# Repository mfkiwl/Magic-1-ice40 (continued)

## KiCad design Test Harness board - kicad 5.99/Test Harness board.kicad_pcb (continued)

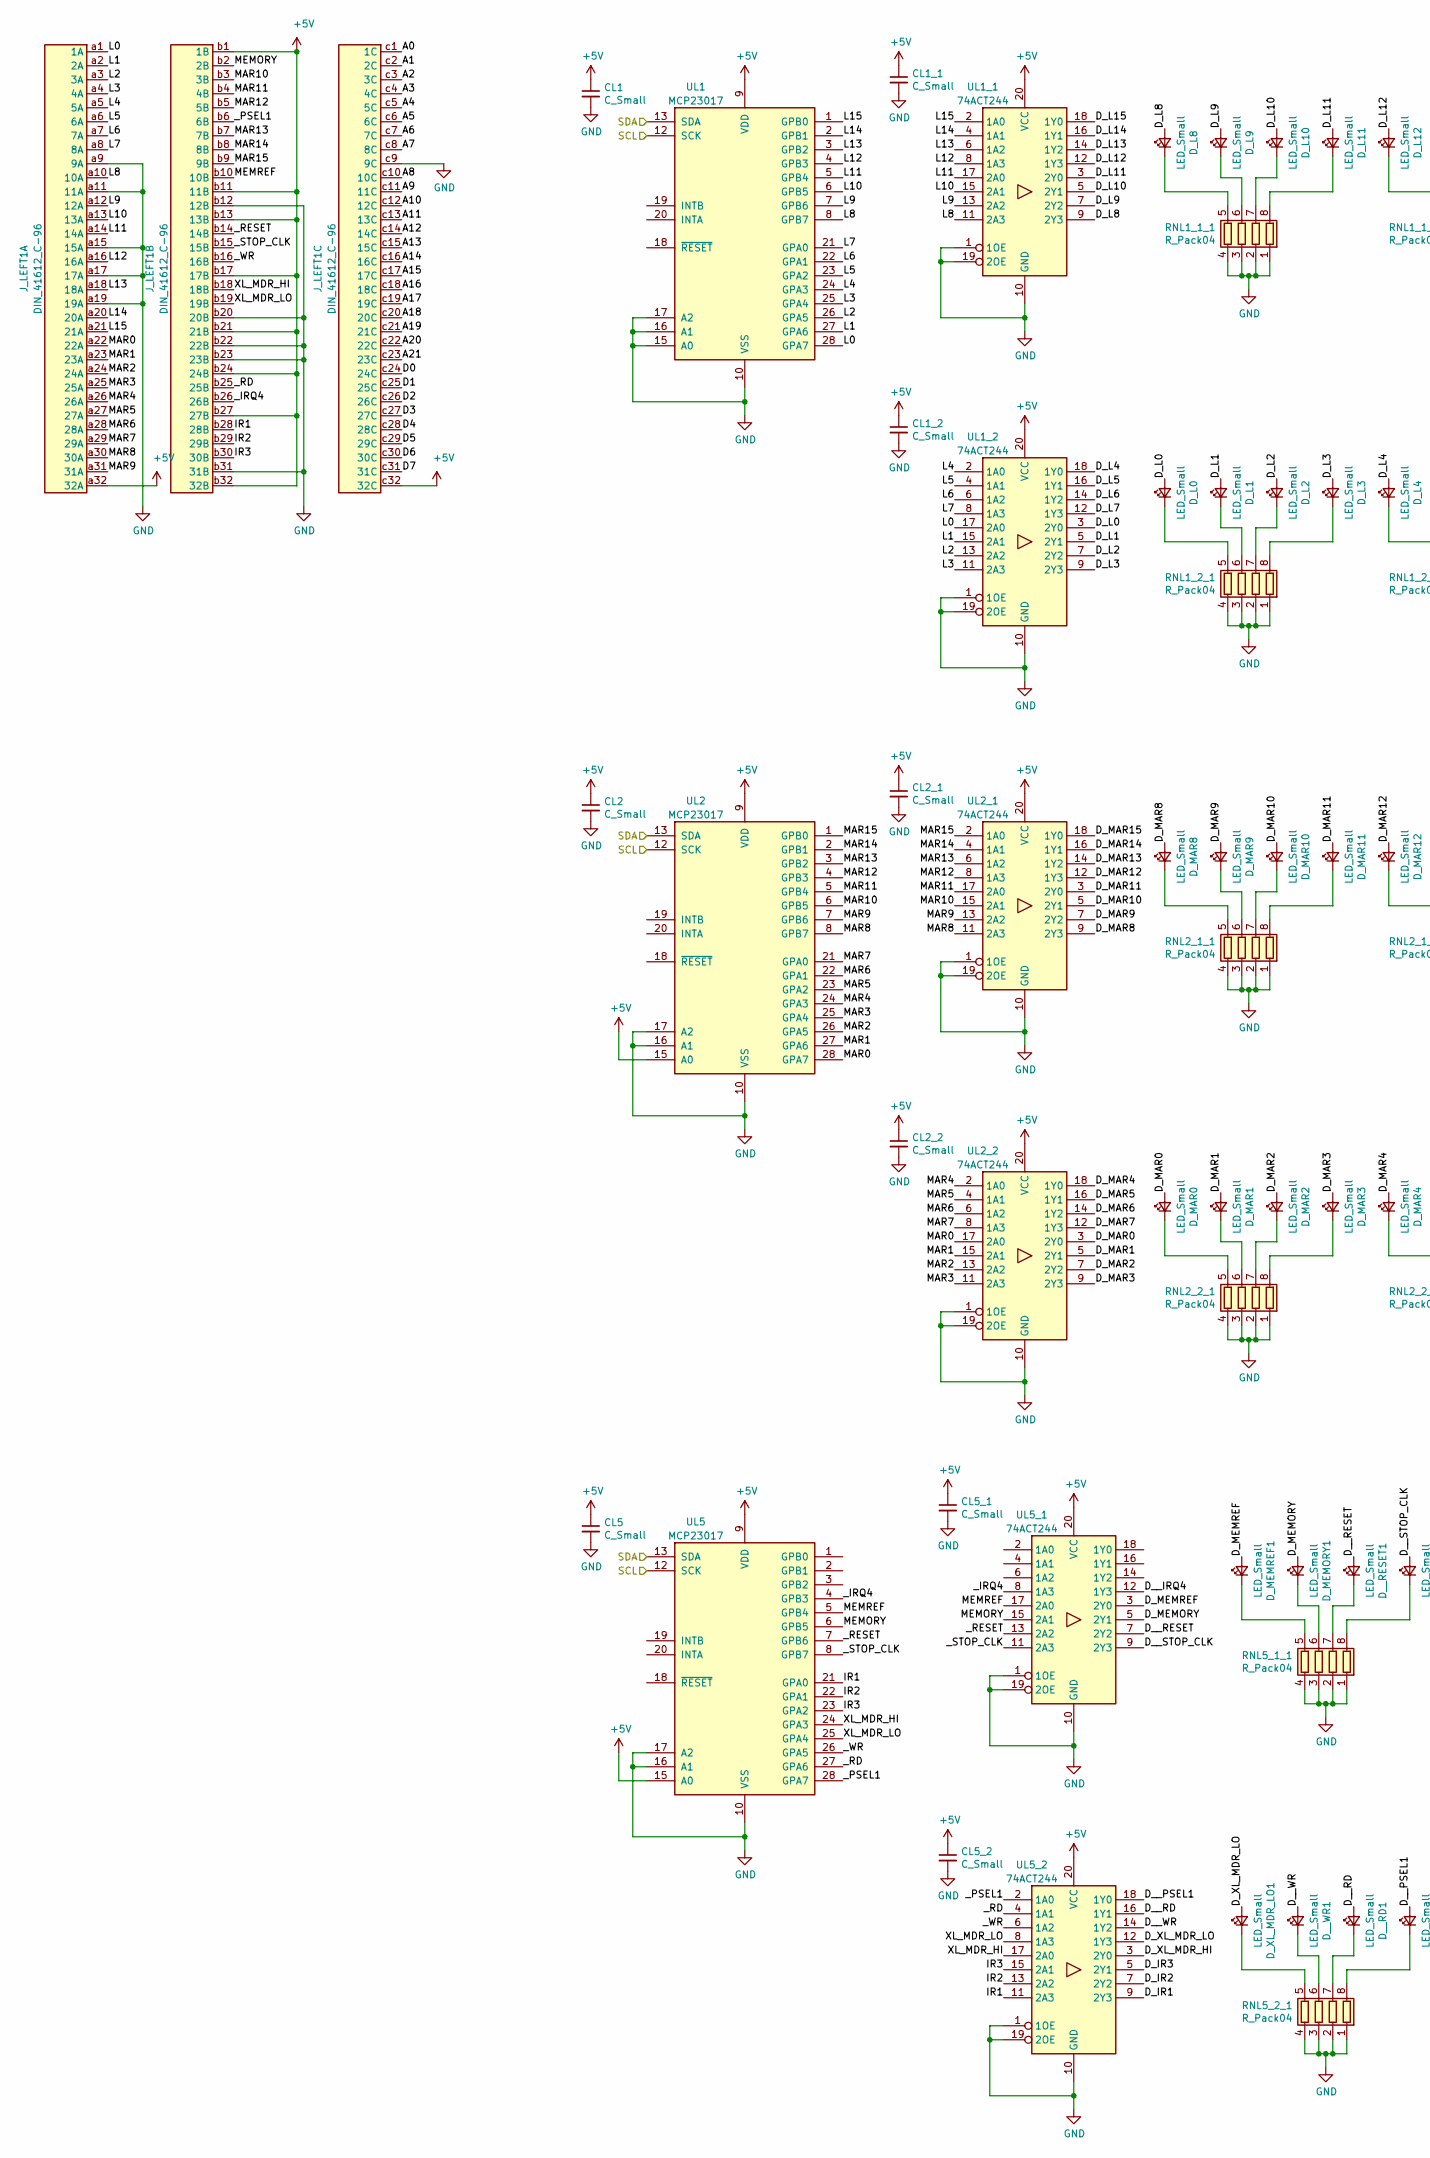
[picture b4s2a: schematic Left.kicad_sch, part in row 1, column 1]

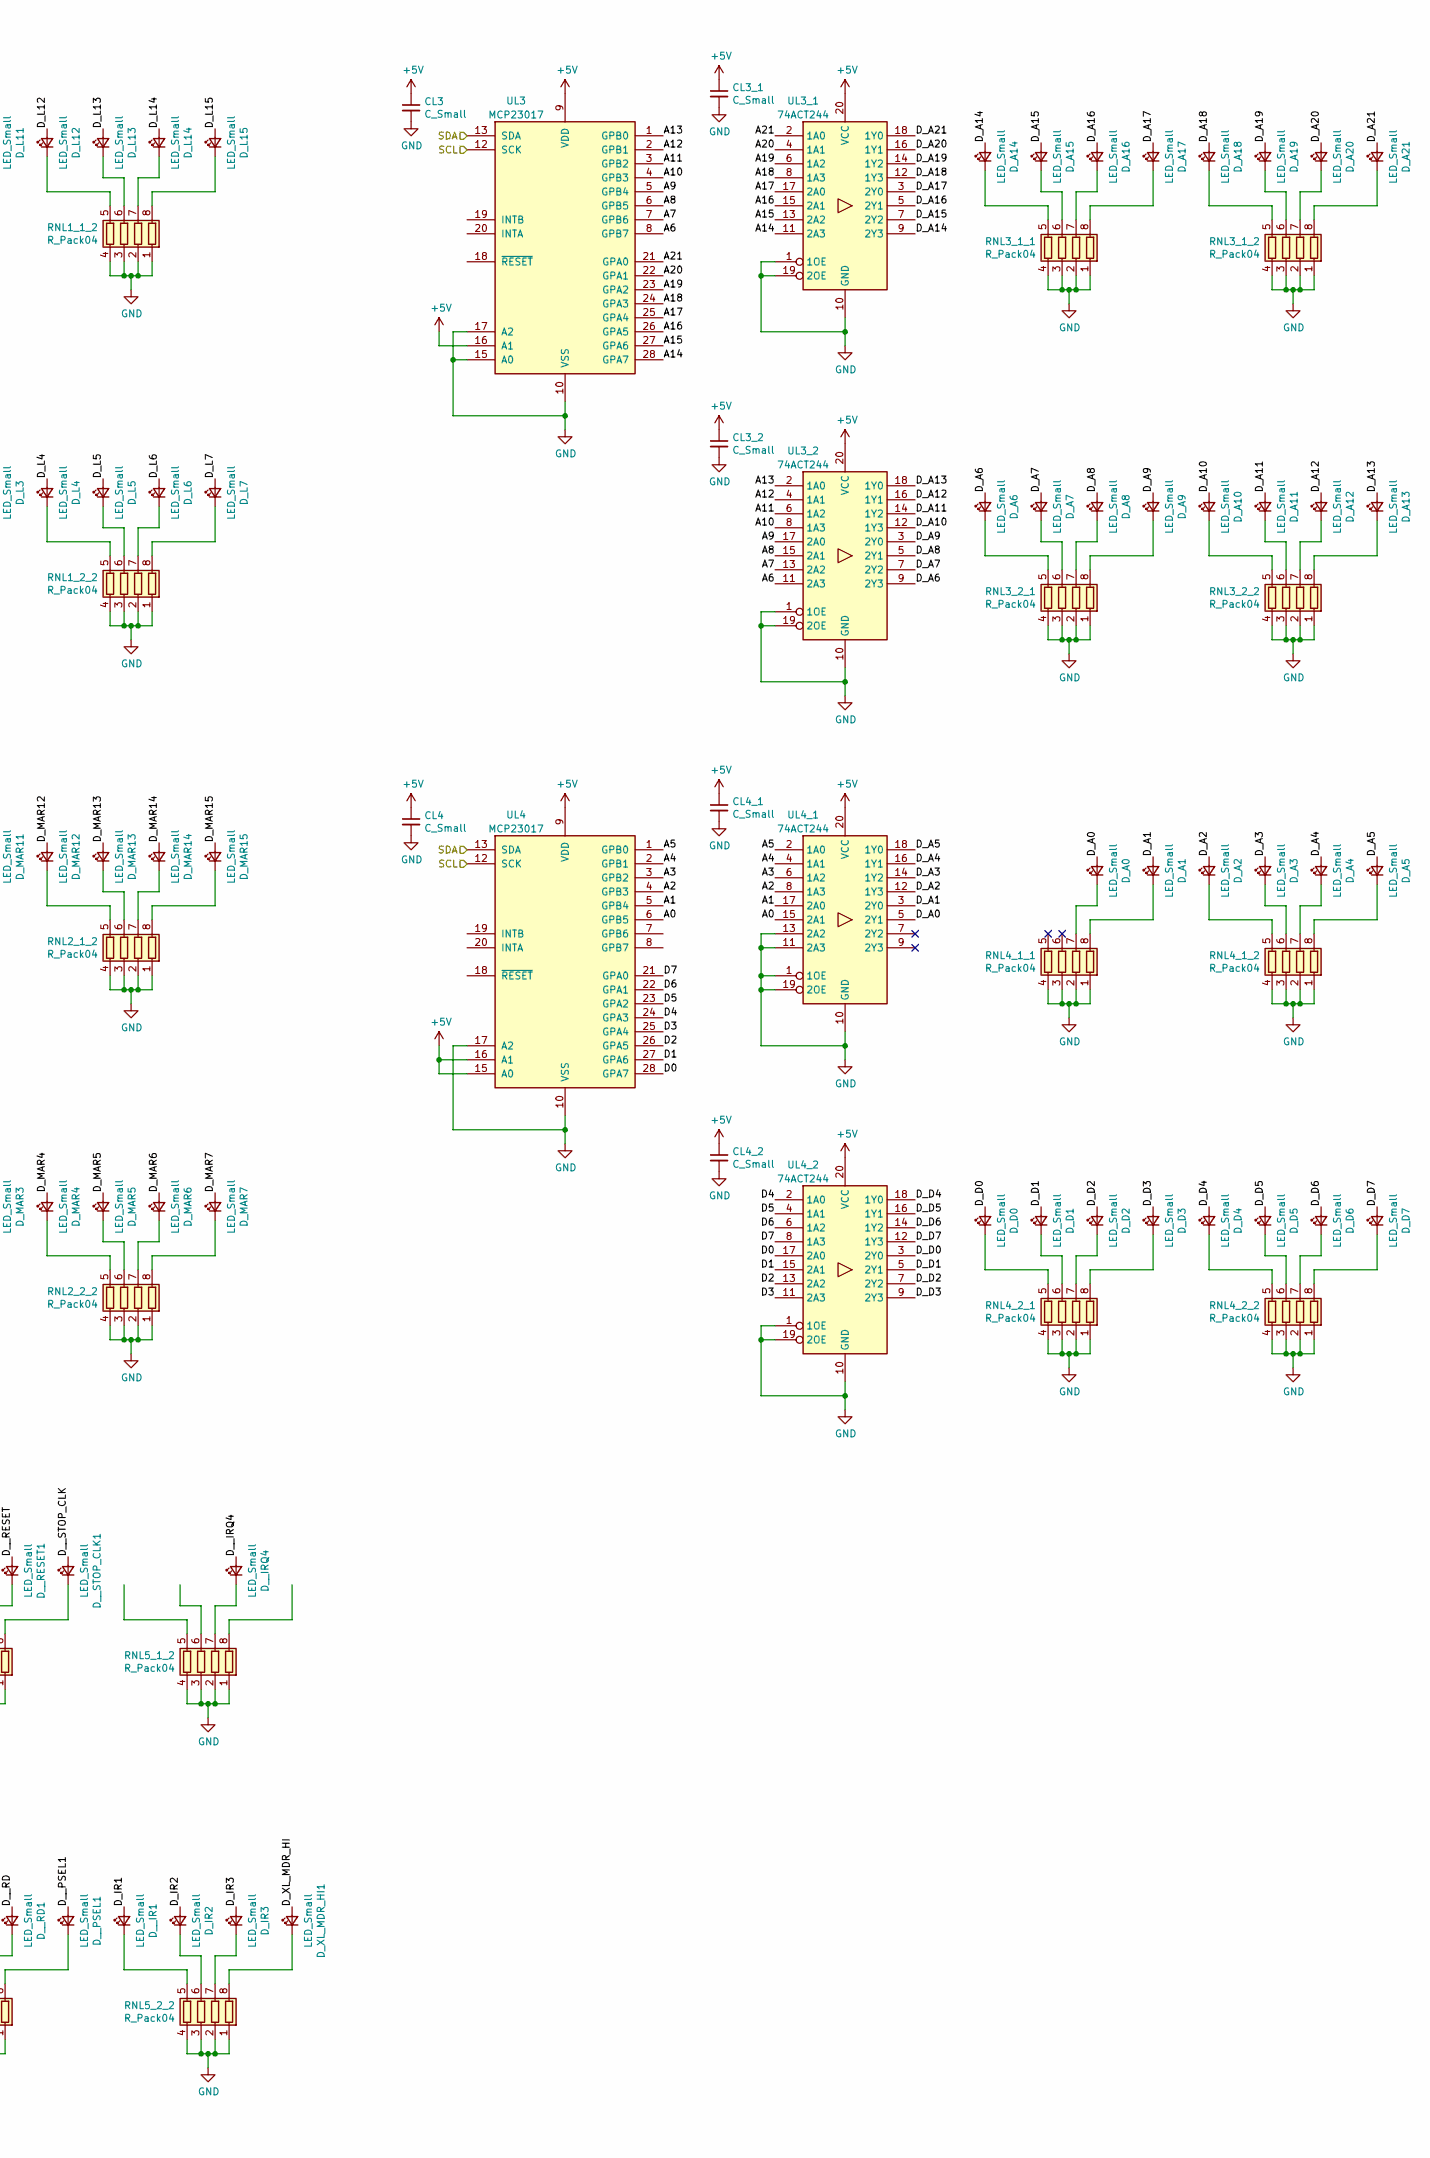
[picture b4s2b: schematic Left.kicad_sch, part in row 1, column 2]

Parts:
CL1, CL1_1, CL1_2, CL2, CL2_1, CL2_2, CL3, CL3_1, CL3_2, CL4, CL4_1, CL4_2, CL5, CL5_1, CL5_2: C_Small; C_1206_3216Metric
D_A0, D_A1, D_A2, D_A3, D_A4, D_A5, D_A6, D_A7, D_A8, D_A9, D_A10, D_A11, D_A12, D_A13, D_A14, D_A15, D_A16, D_A17, D_A18, D_A19, D_A20, D_A21: LED_Small; LED_1206_3216Metric_Castellated; Digikey 160-1167-1-ND
D_D0, D_D1, D_D2, D_D3, D_D4, D_D5, D_D6, D_D7: LED_Small; LED_1206_3216Metric_Castellated; Digikey 160-1167-1-ND
D_IR2, D_IR3: LED_Small; LED_1206_3216Metric_Castellated; Digikey 160-1167-1-ND
D_L0, D_L1, D_L2, D_L3, D_L4, D_L5, D_L6, D_L7, D_L8, D_L9, D_L10, D_L11, D_L12, D_L13, D_L14, D_L15: LED_Small; LED_1206_3216Metric_Castellated; Digikey 160-1167-1-ND
D_MAR0, D_MAR1, D_MAR2, D_MAR3, D_MAR4, D_MAR5, D_MAR6, D_MAR7, D_MAR8, D_MAR9, D_MAR10, D_MAR11, D_MAR12, D_MAR13, D_MAR14, D_MAR15: LED_Small; LED_1206_3216Metric_Castellated; Digikey 160-1167-1-ND
D_MEMORY1: LED_Small; LED_1206_3216Metric_Castellated; Digikey 160-1167-1-ND
D_MEMREF1: LED_Small; LED_1206_3216Metric_Castellated; Digikey 160-1167-1-ND
D_XL_MDR_HI1: LED_Small; LED_1206_3216Metric_Castellated; Digikey 160-1167-1-ND
D_XL_MDR_LO1: LED_Small; LED_1206_3216Metric_Castellated; Digikey 160-1167-1-ND
D__IR1: LED_Small; LED_1206_3216Metric_Castellated; Digikey 160-1167-1-ND
D__IRQ4: LED_Small; LED_1206_3216Metric_Castellated; Digikey 160-1167-1-ND
D__PSEL1: LED_Small; LED_1206_3216Metric_Castellated; Digikey 160-1167-1-ND
D__RD1: LED_Small; LED_1206_3216Metric_Castellated; Digikey 160-1167-1-ND
D__RESET1: LED_Small; LED_1206_3216Metric_Castellated; Digikey 160-1167-1-ND
D__STOP_CLK1: LED_Small; LED_1206_3216Metric_Castellated; Digikey 160-1167-1-ND
D__WR1: LED_Small; LED_1206_3216Metric_Castellated; Digikey 160-1167-1-ND
J_LEFT1: DIN_41612_C-96; DIN41612_C_3x32_Male_Horizontal_THT
RNL1_1_1, RNL1_1_2, RNL1_2_1, RNL1_2_2, RNL2_1_1, RNL2_1_2, RNL2_2_1, RNL2_2_2, RNL3_1_1, RNL3_1_2, RNL3_2_1, RNL3_2_2, RNL4_1_1, RNL4_1_2, RNL4_2_1, RNL4_2_2, RNL5_1_1, RNL5_1_2, RNL5_2_1, RNL5_2_2: R_Pack04; R_Array_Convex_4x1206; Digikey CAY16-331J4LFCT-ND
UL1, UL2, UL3, UL4, UL5: MCP23017; SOIC-28W_7.5x17.9mm_P1.27mm
UL1_1, UL1_2, UL2_1, UL2_2, UL3_1, UL3_2, UL4_1, UL4_2, UL5_1, UL5_2: 74ACT244; SOIC-20W_7.5x12.8mm_P1.27mm; Digikey 296-1071-1-ND

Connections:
+5V: CL1.1, CL1_1.1, CL1_2.1, CL2.1, CL2_1.1, CL2_2.1, CL3.1, CL3_1.1, CL3_2.1, CL4.1, CL4_1.1, CL4_2.1, CL5.1, CL5_1.1, CL5_2.1, J_LEFT1.a32 (32A), J_LEFT1.b1 (1B), J_LEFT1.b11 (11B), J_LEFT1.b13 (13B), J_LEFT1.b17 (17B), J_LEFT1.b21 (21B), J_LEFT1.b24 (24B), J_LEFT1.b27 (27B), J_LEFT1.b32 (32B), J_LEFT1.c32 (32C), UL1.9 (VDD), UL1_1.20 (VCC), UL1_2.20 (VCC), UL2.9 (VDD), UL2.15 (A0), UL2_1.20 (VCC), UL2_2.20 (VCC), UL3.9 (VDD), UL3.16 (A1), UL3_1.20 (VCC), UL3_2.20 (VCC), UL4.9 (VDD), UL4.15 (A0), UL4.16 (A1), UL4_1.20 (VCC), UL4_2.20 (VCC), UL5.9 (VDD), UL5.15 (A0), UL5_1.20 (VCC), UL5_2.20 (VCC); also elsewhere on the board
/Left connector/A0: J_LEFT1.c1 (1C), UL4.6 (GPB5), UL4_1.15 (2A1)
/Left connector/A1: J_LEFT1.c2 (2C), UL4.5 (GPB4), UL4_1.17 (2A0)
/Left connector/A2: J_LEFT1.c3 (3C), UL4.4 (GPB3), UL4_1.8 (1A3)
/Left connector/A3: J_LEFT1.c4 (4C), UL4.3 (GPB2), UL4_1.6 (1A2)
/Left connector/A4: J_LEFT1.c5 (5C), UL4.2 (GPB1), UL4_1.4 (1A1)
/Left connector/A5: J_LEFT1.c6 (6C), UL4.1 (GPB0), UL4_1.2 (1A0)
/Left connector/A6: J_LEFT1.c7 (7C), UL3.8 (GPB7), UL3_2.11 (2A3)
/Left connector/A7: J_LEFT1.c8 (8C), UL3.7 (GPB6), UL3_2.13 (2A2)
/Left connector/A8: J_LEFT1.c10 (10C), UL3.6 (GPB5), UL3_2.15 (2A1)
/Left connector/A9: J_LEFT1.c11 (11C), UL3.5 (GPB4), UL3_2.17 (2A0)
/Left connector/A10: J_LEFT1.c12 (12C), UL3.4 (GPB3), UL3_2.8 (1A3)
/Left connector/A11: J_LEFT1.c13 (13C), UL3.3 (GPB2), UL3_2.6 (1A2)
/Left connector/A12: J_LEFT1.c14 (14C), UL3.2 (GPB1), UL3_2.4 (1A1)
/Left connector/A13: J_LEFT1.c15 (15C), UL3.1 (GPB0), UL3_2.2 (1A0)
/Left connector/A14: J_LEFT1.c16 (16C), UL3.28 (GPA7), UL3_1.11 (2A3)
/Left connector/A15: J_LEFT1.c17 (17C), UL3.27 (GPA6), UL3_1.13 (2A2)
/Left connector/A16: J_LEFT1.c18 (18C), UL3.26 (GPA5), UL3_1.15 (2A1)
/Left connector/A17: J_LEFT1.c19 (19C), UL3.25 (GPA4), UL3_1.17 (2A0)
/Left connector/A18: J_LEFT1.c20 (20C), UL3.24 (GPA3), UL3_1.8 (1A3)
/Left connector/A19: J_LEFT1.c21 (21C), UL3.23 (GPA2), UL3_1.6 (1A2)
/Left connector/A20: J_LEFT1.c22 (22C), UL3.22 (GPA1), UL3_1.4 (1A1)
/Left connector/A21: J_LEFT1.c23 (23C), UL3.21 (GPA0), UL3_1.2 (1A0)
/Left connector/D0: J_LEFT1.c24 (24C), UL4.28 (GPA7), UL4_2.17 (2A0)
/Left connector/D1: J_LEFT1.c25 (25C), UL4.27 (GPA6), UL4_2.15 (2A1)
/Left connector/D2: J_LEFT1.c26 (26C), UL4.26 (GPA5), UL4_2.13 (2A2)
/Left connector/D3: J_LEFT1.c27 (27C), UL4.25 (GPA4), UL4_2.11 (2A3)
/Left connector/D4: J_LEFT1.c28 (28C), UL4.24 (GPA3), UL4_2.2 (1A0)
/Left connector/D5: J_LEFT1.c29 (29C), UL4.23 (GPA2), UL4_2.4 (1A1)
/Left connector/D6: J_LEFT1.c30 (30C), UL4.22 (GPA1), UL4_2.6 (1A2)
/Left connector/D7: J_LEFT1.c31 (31C), UL4.21 (GPA0), UL4_2.8 (1A3)
/Left connector/D_A0: D_A0.2 (A), UL4_1.5 (2Y1)
/Left connector/D_A1: D_A1.2 (A), UL4_1.3 (2Y0)
/Left connector/D_A2: D_A2.2 (A), UL4_1.12 (1Y3)
/Left connector/D_A3: D_A3.2 (A), UL4_1.14 (1Y2)
/Left connector/D_A4: D_A4.2 (A), UL4_1.16 (1Y1)
/Left connector/D_A5: D_A5.2 (A), UL4_1.18 (1Y0)
/Left connector/D_A6: D_A6.2 (A), UL3_2.9 (2Y3)
/Left connector/D_A7: D_A7.2 (A), UL3_2.7 (2Y2)
/Left connector/D_A8: D_A8.2 (A), UL3_2.5 (2Y1)
/Left connector/D_A9: D_A9.2 (A), UL3_2.3 (2Y0)
/Left connector/D_A10: D_A10.2 (A), UL3_2.12 (1Y3)
/Left connector/D_A11: D_A11.2 (A), UL3_2.14 (1Y2)
/Left connector/D_A12: D_A12.2 (A), UL3_2.16 (1Y1)
/Left connector/D_A13: D_A13.2 (A), UL3_2.18 (1Y0)
/Left connector/D_A14: D_A14.2 (A), UL3_1.9 (2Y3)
/Left connector/D_A15: D_A15.2 (A), UL3_1.7 (2Y2)
/Left connector/D_A16: D_A16.2 (A), UL3_1.5 (2Y1)
/Left connector/D_A17: D_A17.2 (A), UL3_1.3 (2Y0)
/Left connector/D_A18: D_A18.2 (A), UL3_1.12 (1Y3)
/Left connector/D_A19: D_A19.2 (A), UL3_1.14 (1Y2)
/Left connector/D_A20: D_A20.2 (A), UL3_1.16 (1Y1)
/Left connector/D_A21: D_A21.2 (A), UL3_1.18 (1Y0)
/Left connector/D_D0: D_D0.2 (A), UL4_2.3 (2Y0)
/Left connector/D_D1: D_D1.2 (A), UL4_2.5 (2Y1)
/Left connector/D_D2: D_D2.2 (A), UL4_2.7 (2Y2)
/Left connector/D_D3: D_D3.2 (A), UL4_2.9 (2Y3)
/Left connector/D_D4: D_D4.2 (A), UL4_2.18 (1Y0)
/Left connector/D_D5: D_D5.2 (A), UL4_2.16 (1Y1)
/Left connector/D_D6: D_D6.2 (A), UL4_2.14 (1Y2)
/Left connector/D_D7: D_D7.2 (A), UL4_2.12 (1Y3)
/Left connector/D_IR1: D__IR1.2 (A), UL5_2.9 (2Y3)
/Left connector/D_IR2: D_IR2.2 (A), UL5_2.7 (2Y2)
/Left connector/D_IR3: D_IR3.2 (A), UL5_2.5 (2Y1)
/Left connector/D_L0: D_L0.2 (A), UL1_2.3 (2Y0)
/Left connector/D_L1: D_L1.2 (A), UL1_2.5 (2Y1)
/Left connector/D_L2: D_L2.2 (A), UL1_2.7 (2Y2)
/Left connector/D_L3: D_L3.2 (A), UL1_2.9 (2Y3)
/Left connector/D_L4: D_L4.2 (A), UL1_2.18 (1Y0)
/Left connector/D_L5: D_L5.2 (A), UL1_2.16 (1Y1)
/Left connector/D_L6: D_L6.2 (A), UL1_2.14 (1Y2)
/Left connector/D_L7: D_L7.2 (A), UL1_2.12 (1Y3)
/Left connector/D_L8: D_L8.2 (A), UL1_1.9 (2Y3)
/Left connector/D_L9: D_L9.2 (A), UL1_1.7 (2Y2)
/Left connector/D_L10: D_L10.2 (A), UL1_1.5 (2Y1)
/Left connector/D_L11: D_L11.2 (A), UL1_1.3 (2Y0)
/Left connector/D_L12: D_L12.2 (A), UL1_1.12 (1Y3)
/Left connector/D_L13: D_L13.2 (A), UL1_1.14 (1Y2)
/Left connector/D_L14: D_L14.2 (A), UL1_1.16 (1Y1)
/Left connector/D_L15: D_L15.2 (A), UL1_1.18 (1Y0)
/Left connector/D_MAR0: D_MAR0.2 (A), UL2_2.3 (2Y0)
/Left connector/D_MAR1: D_MAR1.2 (A), UL2_2.5 (2Y1)
/Left connector/D_MAR2: D_MAR2.2 (A), UL2_2.7 (2Y2)
/Left connector/D_MAR3: D_MAR3.2 (A), UL2_2.9 (2Y3)
/Left connector/D_MAR4: D_MAR4.2 (A), UL2_2.18 (1Y0)
/Left connector/D_MAR5: D_MAR5.2 (A), UL2_2.16 (1Y1)
/Left connector/D_MAR6: D_MAR6.2 (A), UL2_2.14 (1Y2)
/Left connector/D_MAR7: D_MAR7.2 (A), UL2_2.12 (1Y3)
/Left connector/D_MAR8: D_MAR8.2 (A), UL2_1.9 (2Y3)
/Left connector/D_MAR9: D_MAR9.2 (A), UL2_1.7 (2Y2)
/Left connector/D_MAR10: D_MAR10.2 (A), UL2_1.5 (2Y1)
/Left connector/D_MAR11: D_MAR11.2 (A), UL2_1.3 (2Y0)
/Left connector/D_MAR12: D_MAR12.2 (A), UL2_1.12 (1Y3)
/Left connector/D_MAR13: D_MAR13.2 (A), UL2_1.14 (1Y2)
/Left connector/D_MAR14: D_MAR14.2 (A), UL2_1.16 (1Y1)
/Left connector/D_MAR15: D_MAR15.2 (A), UL2_1.18 (1Y0)
/Left connector/D_MEMORY: D_MEMORY1.2 (A), UL5_1.5 (2Y1)
/Left connector/D_MEMREF: D_MEMREF1.2 (A), UL5_1.3 (2Y0)
/Left connector/D_XL_MDR_HI: D_XL_MDR_HI1.2 (A), UL5_2.3 (2Y0)
/Left connector/D_XL_MDR_LO: D_XL_MDR_LO1.2 (A), UL5_2.12 (1Y3)
/Left connector/D__IRQ4: D__IRQ4.2 (A), UL5_1.12 (1Y3)
/Left connector/D__PSEL1: D__PSEL1.2 (A), UL5_2.18 (1Y0)
/Left connector/D__RD: D__RD1.2 (A), UL5_2.16 (1Y1)
/Left connector/D__RESET: D__RESET1.2 (A), UL5_1.7 (2Y2)
/Left connector/D__STOP_CLK: D__STOP_CLK1.2 (A), UL5_1.9 (2Y3)
/Left connector/D__WR: D__WR1.2 (A), UL5_2.14 (1Y2)
/Left connector/IR1: J_LEFT1.b28 (28B), UL5.21 (GPA0), UL5_2.11 (2A3)
/Left connector/IR2: J_LEFT1.b29 (29B), UL5.22 (GPA1), UL5_2.13 (2A2)
/Left connector/IR3: J_LEFT1.b30 (30B), UL5.23 (GPA2), UL5_2.15 (2A1)
/Left connector/L0: J_LEFT1.a1 (1A), UL1.28 (GPA7), UL1_2.17 (2A0)
/Left connector/L1: J_LEFT1.a2 (2A), UL1.27 (GPA6), UL1_2.15 (2A1)
/Left connector/L2: J_LEFT1.a3 (3A), UL1.26 (GPA5), UL1_2.13 (2A2)
/Left connector/L3: J_LEFT1.a4 (4A), UL1.25 (GPA4), UL1_2.11 (2A3)
/Left connector/L4: J_LEFT1.a5 (5A), UL1.24 (GPA3), UL1_2.2 (1A0)
/Left connector/L5: J_LEFT1.a6 (6A), UL1.23 (GPA2), UL1_2.4 (1A1)
/Left connector/L6: J_LEFT1.a7 (7A), UL1.22 (GPA1), UL1_2.6 (1A2)
/Left connector/L7: J_LEFT1.a8 (8A), UL1.21 (GPA0), UL1_2.8 (1A3)
/Left connector/L8: J_LEFT1.a10 (10A), UL1.8 (GPB7), UL1_1.11 (2A3)
/Left connector/L9: J_LEFT1.a12 (12A), UL1.7 (GPB6), UL1_1.13 (2A2)
/Left connector/L10: J_LEFT1.a13 (13A), UL1.6 (GPB5), UL1_1.15 (2A1)
/Left connector/L11: J_LEFT1.a14 (14A), UL1.5 (GPB4), UL1_1.17 (2A0)
/Left connector/L12: J_LEFT1.a16 (16A), UL1.4 (GPB3), UL1_1.8 (1A3)
/Left connector/L13: J_LEFT1.a18 (18A), UL1.3 (GPB2), UL1_1.6 (1A2)
/Left connector/L14: J_LEFT1.a20 (20A), UL1.2 (GPB1), UL1_1.4 (1A1)
/Left connector/L15: J_LEFT1.a21 (21A), UL1.1 (GPB0), UL1_1.2 (1A0)
/Left connector/MAR0: J_LEFT1.a22 (22A), UL2.28 (GPA7), UL2_2.17 (2A0)
/Left connector/MAR1: J_LEFT1.a23 (23A), UL2.27 (GPA6), UL2_2.15 (2A1)
/Left connector/MAR2: J_LEFT1.a24 (24A), UL2.26 (GPA5), UL2_2.13 (2A2)
/Left connector/MAR3: J_LEFT1.a25 (25A), UL2.25 (GPA4), UL2_2.11 (2A3)
/Left connector/MAR4: J_LEFT1.a26 (26A), UL2.24 (GPA3), UL2_2.2 (1A0)
/Left connector/MAR5: J_LEFT1.a27 (27A), UL2.23 (GPA2), UL2_2.4 (1A1)
/Left connector/MAR6: J_LEFT1.a28 (28A), UL2.22 (GPA1), UL2_2.6 (1A2)
/Left connector/MAR7: J_LEFT1.a29 (29A), UL2.21 (GPA0), UL2_2.8 (1A3)
/Left connector/MAR8: J_LEFT1.a30 (30A), UL2.8 (GPB7), UL2_1.11 (2A3)
/Left connector/MAR9: J_LEFT1.a31 (31A), UL2.7 (GPB6), UL2_1.13 (2A2)
/Left connector/MAR10: J_LEFT1.b3 (3B), UL2.6 (GPB5), UL2_1.15 (2A1)
/Left connector/MAR11: J_LEFT1.b4 (4B), UL2.5 (GPB4), UL2_1.17 (2A0)
/Left connector/MAR12: J_LEFT1.b5 (5B), UL2.4 (GPB3), UL2_1.8 (1A3)
/Left connector/MAR13: J_LEFT1.b7 (7B), UL2.3 (GPB2), UL2_1.6 (1A2)
/Left connector/MAR14: J_LEFT1.b8 (8B), UL2.2 (GPB1), UL2_1.4 (1A1)
/Left connector/MAR15: J_LEFT1.b9 (9B), UL2.1 (GPB0), UL2_1.2 (1A0)
/Left connector/MEMORY: J_LEFT1.b2 (2B), UL5.6 (GPB5), UL5_1.15 (2A1)
/Left connector/MEMREF: J_LEFT1.b10 (10B), UL5.5 (GPB4), UL5_1.17 (2A0)
/Left connector/SCL: UL1.12 (SCK), UL2.12 (SCK), UL3.12 (SCK), UL4.12 (SCK), UL5.12 (SCK)
/Left connector/SDA: UL1.13 (SDA), UL2.13 (SDA), UL3.13 (SDA), UL4.13 (SDA), UL5.13 (SDA)
/Left connector/XL_MDR_HI: J_LEFT1.b18 (18B), UL5.24 (GPA3), UL5_2.17 (2A0)
/Left connector/XL_MDR_LO: J_LEFT1.b19 (19B), UL5.25 (GPA4), UL5_2.8 (1A3)
/Left connector/_IRQ4: J_LEFT1.b26 (26B), UL5.4 (GPB3), UL5_1.8 (1A3)
/Left connector/_PSEL1: J_LEFT1.b6 (6B), UL5.28 (GPA7), UL5_2.2 (1A0)
/Left connector/_RD: J_LEFT1.b25 (25B), UL5.27 (GPA6), UL5_2.4 (1A1)
/Left connector/_RESET: J_LEFT1.b14 (14B), UL5.7 (GPB6), UL5_1.13 (2A2)
/Left connector/_STOP_CLK: J_LEFT1.b15 (15B), UL5.8 (GPB7), UL5_1.11 (2A3)
/Left connector/_WR: J_LEFT1.b16 (16B), UL5.26 (GPA5), UL5_2.6 (1A2)
GND: CL1.2, CL1_1.2, CL1_2.2, CL2.2, CL2_1.2, CL2_2.2, CL3.2, CL3_1.2, CL3_2.2, CL4.2, CL4_1.2, CL4_2.2, CL5.2, CL5_1.2, CL5_2.2, J_LEFT1.a9 (9A), J_LEFT1.a11 (11A), J_LEFT1.a15 (15A), J_LEFT1.a17 (17A), J_LEFT1.a19 (19A), J_LEFT1.b12 (12B), J_LEFT1.b20 (20B), J_LEFT1.b22 (22B), J_LEFT1.b23 (23B), J_LEFT1.b31 (31B), J_LEFT1.c9 (9C), RNL1_1_1.1 (R1.1), RNL1_1_1.2 (R2.1), RNL1_1_1.3 (R3.1), RNL1_1_1.4 (R4.1), RNL1_1_2.1 (R1.1), RNL1_1_2.2 (R2.1), RNL1_1_2.3 (R3.1), RNL1_1_2.4 (R4.1), RNL1_2_1.1 (R1.1), RNL1_2_1.2 (R2.1), RNL1_2_1.3 (R3.1), RNL1_2_1.4 (R4.1), RNL1_2_2.1 (R1.1), RNL1_2_2.2 (R2.1), RNL1_2_2.3 (R3.1), RNL1_2_2.4 (R4.1), RNL2_1_1.1 (R1.1), RNL2_1_1.2 (R2.1), RNL2_1_1.3 (R3.1), RNL2_1_1.4 (R4.1), RNL2_1_2.1 (R1.1), RNL2_1_2.2 (R2.1), RNL2_1_2.3 (R3.1), RNL2_1_2.4 (R4.1), RNL2_2_1.1 (R1.1), RNL2_2_1.2 (R2.1), RNL2_2_1.3 (R3.1), RNL2_2_1.4 (R4.1), RNL2_2_2.1 (R1.1), RNL2_2_2.2 (R2.1), RNL2_2_2.3 (R3.1), RNL2_2_2.4 (R4.1), RNL3_1_1.1 (R1.1), RNL3_1_1.2 (R2.1), RNL3_1_1.3 (R3.1), RNL3_1_1.4 (R4.1), RNL3_1_2.1 (R1.1), RNL3_1_2.2 (R2.1), RNL3_1_2.3 (R3.1), RNL3_1_2.4 (R4.1), RNL3_2_1.1 (R1.1), RNL3_2_1.2 (R2.1), RNL3_2_1.3 (R3.1), RNL3_2_1.4 (R4.1), RNL3_2_2.1 (R1.1), RNL3_2_2.2 (R2.1), RNL3_2_2.3 (R3.1), RNL3_2_2.4 (R4.1), RNL4_1_1.1 (R1.1), RNL4_1_1.2 (R2.1), RNL4_1_1.3 (R3.1), RNL4_1_1.4 (R4.1), RNL4_1_2.1 (R1.1), RNL4_1_2.2 (R2.1), RNL4_1_2.3 (R3.1), RNL4_1_2.4 (R4.1), RNL4_2_1.1 (R1.1), RNL4_2_1.2 (R2.1), RNL4_2_1.3 (R3.1), RNL4_2_1.4 (R4.1), RNL4_2_2.1 (R1.1), RNL4_2_2.2 (R2.1), RNL4_2_2.3 (R3.1), RNL4_2_2.4 (R4.1), RNL5_1_1.1 (R1.1), RNL5_1_1.2 (R2.1), RNL5_1_1.3 (R3.1), RNL5_1_1.4 (R4.1), RNL5_1_2.1 (R1.1), RNL5_1_2.2 (R2.1), RNL5_1_2.3 (R3.1), RNL5_1_2.4 (R4.1), RNL5_2_1.1 (R1.1), RNL5_2_1.2 (R2.1), RNL5_2_1.3 (R3.1), RNL5_2_1.4 (R4.1), RNL5_2_2.1 (R1.1), RNL5_2_2.2 (R2.1), RNL5_2_2.3 (R3.1), RNL5_2_2.4 (R4.1), UL1.10 (VSS), UL1.15 (A0), UL1.16 (A1), UL1.17 (A2), UL1_1.1 (1OE), UL1_1.10 (GND), UL1_1.19 (2OE), UL1_2.1 (1OE), UL1_2.10 (GND), UL1_2.19 (2OE), UL2.10 (VSS), UL2.16 (A1), UL2.17 (A2), UL2_1.1 (1OE), UL2_1.10 (GND), UL2_1.19 (2OE), UL2_2.1 (1OE), UL2_2.10 (GND), UL2_2.19 (2OE), UL3.10 (VSS), UL3.15 (A0), UL3.17 (A2), UL3_1.1 (1OE), UL3_1.10 (GND), UL3_1.19 (2OE), UL3_2.1 (1OE), UL3_2.10 (GND), UL3_2.19 (2OE), UL4.10 (VSS), UL4.17 (A2), UL4_1.1 (1OE), UL4_1.10 (GND), UL4_1.11 (2A3), UL4_1.13 (2A2), UL4_1.19 (2OE), UL4_2.1 (1OE), UL4_2.10 (GND), UL4_2.19 (2OE), UL5.10 (VSS), UL5.16 (A1), UL5.17 (A2), UL5_1.1 (1OE), UL5_1.10 (GND), UL5_1.19 (2OE), UL5_2.1 (1OE), UL5_2.10 (GND), UL5_2.19 (2OE); also elsewhere on the board
unnamed: D_A0.1 (K), RNL4_1_1.7 (R2.2)
unnamed: D_A1.1 (K), RNL4_1_1.8 (R1.2)
unnamed: D_A2.1 (K), RNL4_1_2.5 (R4.2)
unnamed: D_A3.1 (K), RNL4_1_2.6 (R3.2)
unnamed: D_A4.1 (K), RNL4_1_2.7 (R2.2)
unnamed: D_A5.1 (K), RNL4_1_2.8 (R1.2)
unnamed: D_A6.1 (K), RNL3_2_1.5 (R4.2)
unnamed: D_A7.1 (K), RNL3_2_1.6 (R3.2)
unnamed: D_A8.1 (K), RNL3_2_1.7 (R2.2)
unnamed: D_A9.1 (K), RNL3_2_1.8 (R1.2)
unnamed: D_A10.1 (K), RNL3_2_2.5 (R4.2)
unnamed: D_A11.1 (K), RNL3_2_2.6 (R3.2)
unnamed: D_A12.1 (K), RNL3_2_2.7 (R2.2)
unnamed: D_A13.1 (K), RNL3_2_2.8 (R1.2)
unnamed: D_A14.1 (K), RNL3_1_1.5 (R4.2)
unnamed: D_A15.1 (K), RNL3_1_1.6 (R3.2)
unnamed: D_A16.1 (K), RNL3_1_1.7 (R2.2)
unnamed: D_A17.1 (K), RNL3_1_1.8 (R1.2)
unnamed: D_A18.1 (K), RNL3_1_2.5 (R4.2)
unnamed: D_A19.1 (K), RNL3_1_2.6 (R3.2)
unnamed: D_A20.1 (K), RNL3_1_2.7 (R2.2)
unnamed: D_A21.1 (K), RNL3_1_2.8 (R1.2)
unnamed: D_D0.1 (K), RNL4_2_1.5 (R4.2)
unnamed: D_D1.1 (K), RNL4_2_1.6 (R3.2)
unnamed: D_D2.1 (K), RNL4_2_1.7 (R2.2)
unnamed: D_D3.1 (K), RNL4_2_1.8 (R1.2)
unnamed: D_D4.1 (K), RNL4_2_2.5 (R4.2)
unnamed: D_D5.1 (K), RNL4_2_2.6 (R3.2)
unnamed: D_D6.1 (K), RNL4_2_2.7 (R2.2)
unnamed: D_D7.1 (K), RNL4_2_2.8 (R1.2)
unnamed: D_IR2.1 (K), RNL5_2_2.6 (R3.2)
unnamed: D_IR3.1 (K), RNL5_2_2.7 (R2.2)
unnamed: D_L0.1 (K), RNL1_2_1.5 (R4.2)
unnamed: D_L1.1 (K), RNL1_2_1.6 (R3.2)
unnamed: D_L2.1 (K), RNL1_2_1.7 (R2.2)
unnamed: D_L3.1 (K), RNL1_2_1.8 (R1.2)
unnamed: D_L4.1 (K), RNL1_2_2.5 (R4.2)
unnamed: D_L5.1 (K), RNL1_2_2.6 (R3.2)
unnamed: D_L6.1 (K), RNL1_2_2.7 (R2.2)
unnamed: D_L7.1 (K), RNL1_2_2.8 (R1.2)
unnamed: D_L8.1 (K), RNL1_1_1.5 (R4.2)
unnamed: D_L9.1 (K), RNL1_1_1.6 (R3.2)
unnamed: D_L10.1 (K), RNL1_1_1.7 (R2.2)
unnamed: D_L11.1 (K), RNL1_1_1.8 (R1.2)
unnamed: D_L12.1 (K), RNL1_1_2.5 (R4.2)
unnamed: D_L13.1 (K), RNL1_1_2.6 (R3.2)
unnamed: D_L14.1 (K), RNL1_1_2.7 (R2.2)
unnamed: D_L15.1 (K), RNL1_1_2.8 (R1.2)
unnamed: D_MAR0.1 (K), RNL2_2_1.5 (R4.2)
unnamed: D_MAR1.1 (K), RNL2_2_1.6 (R3.2)
unnamed: D_MAR2.1 (K), RNL2_2_1.7 (R2.2)
unnamed: D_MAR3.1 (K), RNL2_2_1.8 (R1.2)
unnamed: D_MAR4.1 (K), RNL2_2_2.5 (R4.2)
unnamed: D_MAR5.1 (K), RNL2_2_2.6 (R3.2)
unnamed: D_MAR6.1 (K), RNL2_2_2.7 (R2.2)
unnamed: D_MAR7.1 (K), RNL2_2_2.8 (R1.2)
unnamed: D_MAR8.1 (K), RNL2_1_1.5 (R4.2)
unnamed: D_MAR9.1 (K), RNL2_1_1.6 (R3.2)
unnamed: D_MAR10.1 (K), RNL2_1_1.7 (R2.2)
unnamed: D_MAR11.1 (K), RNL2_1_1.8 (R1.2)
unnamed: D_MAR12.1 (K), RNL2_1_2.5 (R4.2)
unnamed: D_MAR13.1 (K), RNL2_1_2.6 (R3.2)
unnamed: D_MAR14.1 (K), RNL2_1_2.7 (R2.2)
unnamed: D_MAR15.1 (K), RNL2_1_2.8 (R1.2)
unnamed: D_MEMORY1.1 (K), RNL5_1_1.6 (R3.2)
unnamed: D_MEMREF1.1 (K), RNL5_1_1.5 (R4.2)
unnamed: D_XL_MDR_HI1.1 (K), RNL5_2_2.8 (R1.2)
unnamed: D_XL_MDR_LO1.1 (K), RNL5_2_1.5 (R4.2)
unnamed: D__IR1.1 (K), RNL5_2_2.5 (R4.2)
unnamed: D__IRQ4.1 (K), RNL5_1_2.7 (R2.2)
unnamed: D__PSEL1.1 (K), RNL5_2_1.8 (R1.2)
unnamed: D__RD1.1 (K), RNL5_2_1.7 (R2.2)
unnamed: D__RESET1.1 (K), RNL5_1_1.7 (R2.2)
unnamed: D__STOP_CLK1.1 (K), RNL5_1_1.8 (R1.2)
unnamed: D__WR1.1 (K), RNL5_2_1.6 (R3.2)

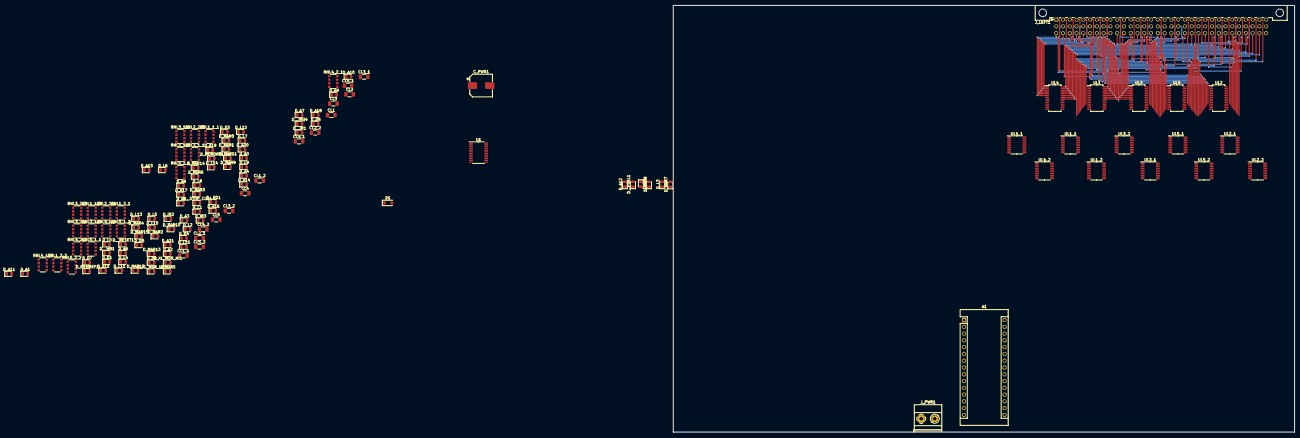
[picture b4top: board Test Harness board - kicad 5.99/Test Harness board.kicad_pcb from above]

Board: 4 copper layers, 233.0 x 160.0 mm, 131 parts (0 on the bottom side), 232 nets.

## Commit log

2020-08-30 add the ALU and general registers board
2020-08-30 fix typo
2020-09-02 added a buffer on the _RESET line, which is rather loaded
2020-09-03 Start on the test harness board
2020-09-03 Starting the test harness board
2020-09-03 add the components to display the MAR bits
2020-09-04 restart on the test harness, made a more compact design (will need the 4 layers though)
2020-09-06 restart with the test harness board
2020-09-07 oops, had the connector on the wrong side !
2020-09-07 fix via to via distance according to the rules, hope that works
2020-09-07 fix via-via distance according to JLCPCB rules
2020-09-08 muck around with component placement
2020-09-08 muck around with board setup
2020-09-10 move ALU board to a versionned directory
2020-09-12 re-routed the ALU board, with better default nets (looks much better)
2020-09-13 fix major mistake, JLEFT1 and JRIGHT1 were reversed
2020-09-13 button up all missing things, generate groundplanes on all signal layers
2020-09-13 rename the test harness directory
2020-09-14 route the left connector of test_harness board
2020-09-15 the left connector side of the test harness is in good shape.. even discovered that we can have those HP displays now made by broadcom
2020-09-16 added a bunch of things, including board under test power control
2020-09-17 reduced the lenght and optimize the path for _L_MODE
2020-09-17 fix stuff, add series resistor on clock line ohms)
2020-09-17 fix lots of tiny details
2020-09-17 add missing libraries
2020-09-17 more fixes
2020-09-18 position the last leds of the left side
2020-09-18 added a power LED
2020-09-18 change all caps to 0805
2020-09-18 update the ground planes
2020-09-20 add memory component, fix a few things
2020-09-20 start of the control card schematics
2020-09-20 add buffers for the write to the µCODE stuff
2020-09-20 add the µcode output registers
2020-09-20 add the µcode data write registers
2020-09-20 add board cutlines
2020-09-20 connect the enable lines for the µcode rams
2020-09-20 add what I think are the necessary lines to control writing to the µcode store
2020-09-20 move the '273 to save space on the scematic
2020-09-20 add docs
2020-09-20 add the magic-1 original schematics
2020-09-20 bits of the devices card
2020-09-20 add the extra components file
2020-09-20 some updates to the PCB (no idea what)
2020-09-20 add an ESP32 as a service processor
2020-09-20 fix power and other stuff
2020-09-20 add lots of nets to the Din connectors
